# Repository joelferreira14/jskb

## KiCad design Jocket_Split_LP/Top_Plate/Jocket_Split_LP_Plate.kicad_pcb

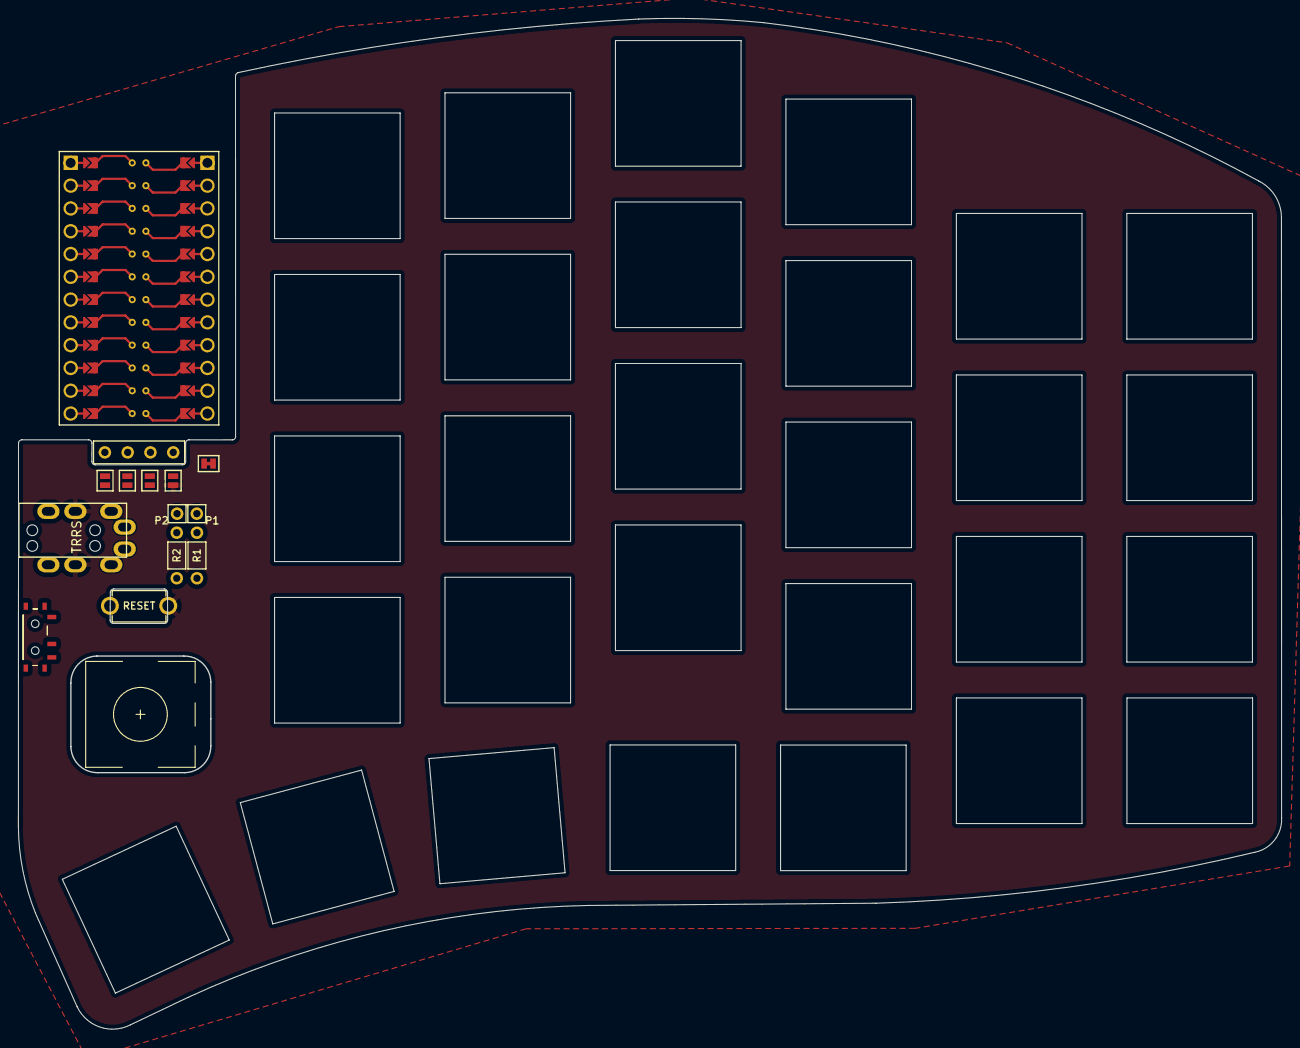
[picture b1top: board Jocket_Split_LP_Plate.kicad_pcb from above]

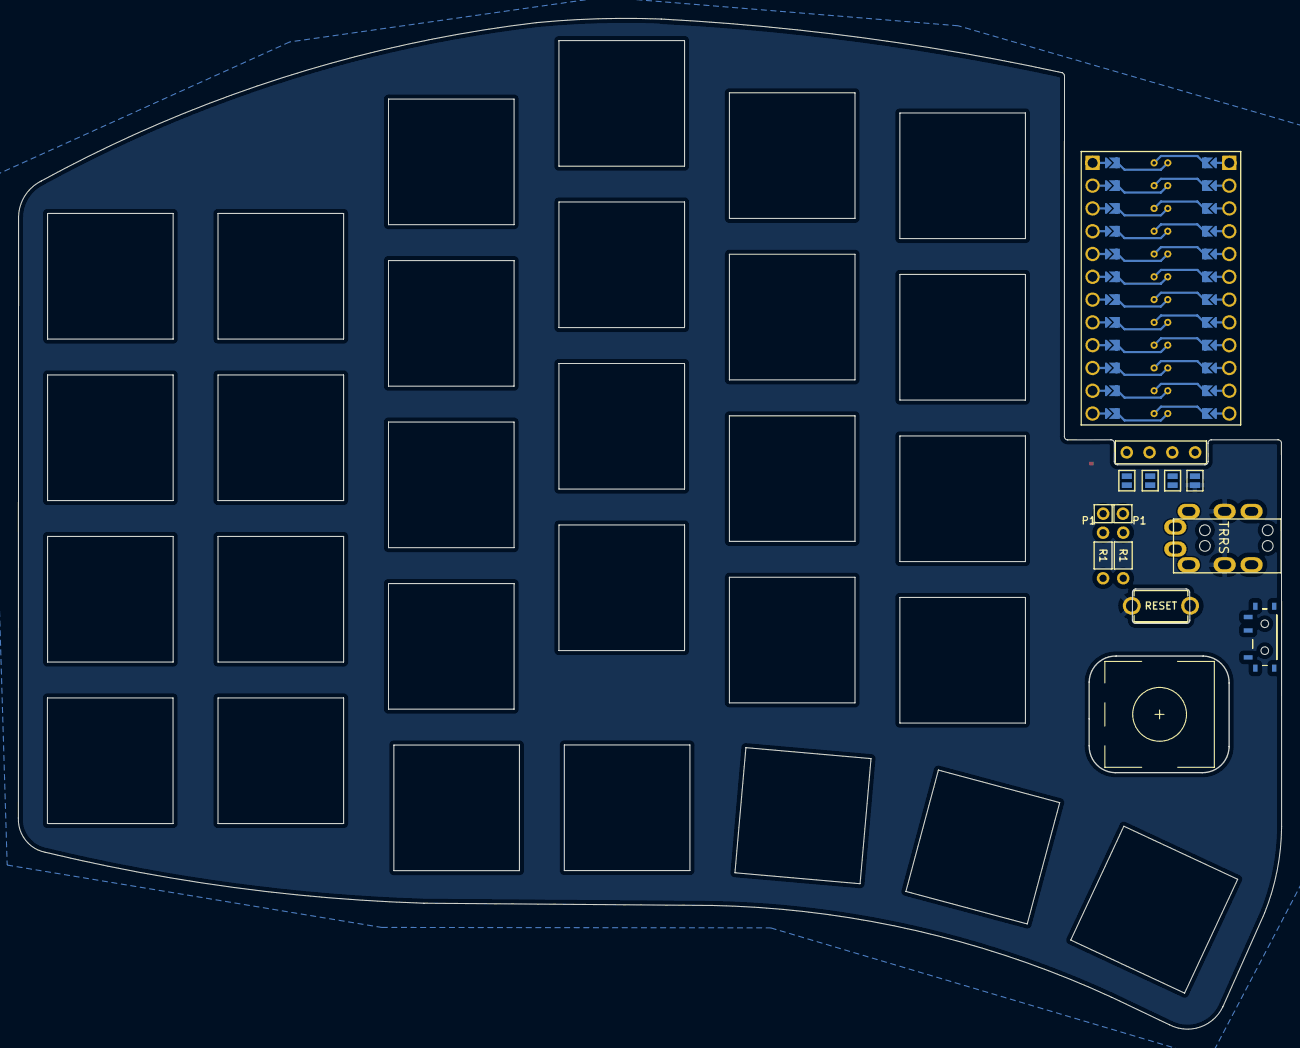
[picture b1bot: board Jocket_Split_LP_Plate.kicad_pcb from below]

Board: 2 copper layers, 140.8 x 112.7 mm, 48 parts (4 on the bottom side), 13 nets, no tracks yet.

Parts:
J2: 4PIN; MJ-4PP-9
J3: OLED; OLED_4Pin
JP1, JP2, JP3, JP4, JP5, JP6, JP7, JP8: Jumper_NO_Small; Jumper
P1, P2: i2c_pin; 1pin_conn
R1, R2: R; RESISTOR_mini
RSW1: SW_RST; TACT_SWITCH_TVBP06
S31: switch_MSK12C02; Switch_MSK12C02_DoubleSided
SW1, SW2, SW3, SW4, SW5, SW6, SW7, SW8, SW9, SW10, SW11, SW12, SW13, SW14, SW15, SW16, SW17, SW18, SW19, SW20, SW21, SW22, SW23, SW24, SW26, SW27, SW28, SW29, SW30: SW_PUSH_LED; Plate_ChocSpacing_Hotswap_SK6812MiniE
SW25: Rotary_Encoder_Switch; Plate_RotaryEncoder_Alps_EC11E-Switch_Vertical
U1: ProMicro
W1: jumper; jumper_data

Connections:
/i2c_c: J2.4, P1.1
/i2c_d: J2.3, P2.1, W1.2
Bat+: S31.B1 (COM), U1.24 (RAW)
DATA: U1.2 (RX(PD2)), W1.1
GND: J2.2, JP1.2, JP8.2, RSW1.1, U1.3 (GND), U1.4 (GND), U1.23 (GND)
unnamed: J3.1, JP4.1, JP8.1
unnamed: J3.2, JP3.1, JP7.1
unnamed: J3.3, JP2.1, JP6.1
unnamed: J3.4, JP1.1, JP5.1
RESET: RSW1.2, U1.22 (RST)
SCL: JP3.2, JP6.2, R2.2, U1.6 (SCL(PD0))
SDA: JP4.2, JP5.2, R1.2, U1.5 (SDA(PD1))
VCC: J2.1, JP2.2, JP7.2, R1.1, R2.1, U1.21 (VCC)

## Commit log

2022-07-16 Initial commit
    :D
2022-10-27 Remaking the case and Plate
    Now that I got all components I realized what I need to change to make everything fit.
    Changes that I pretend to make:
    1. Add a lid to the case for the PCB+plate "snap" in place.
    2. Symmetric rubber feet placement.
    3. Enlarge the USB connector hole/socket
    4. Maybe add some branding to the bottom of the case.
2022-10-29 Case test model completed.
2022-11-13 V0.1
    It works but needs some tweaks ;)
2022-11-13 General placement for components
    Components in place, next step: routing
2022-11-13 Traces and case updated
2022-11-14 Increase size of usb cutout (case)
2023-02-12 After a break, resuming the dev
2023-03-25 Case Improvements
